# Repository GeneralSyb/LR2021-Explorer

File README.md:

# LR2021-Explorer
A small development board for Semtech's LR2021 4th generation LoRa transceiver.

## References
This design is based on the publicly available reference design available at:
https://www.semtech.com/products/wireless-rf/lora-plus/lr2021
The design uses a direct-tie implementation, which means there is no RF switch to switch between RX and TX mode. The reduces the component count, possibly at the loss of some performance.

## Testing
There is no Arduino-style library available yet, but some people are working on adding support for the chip in the RadioLib library. Therefore it is not know if this board actually works or not.

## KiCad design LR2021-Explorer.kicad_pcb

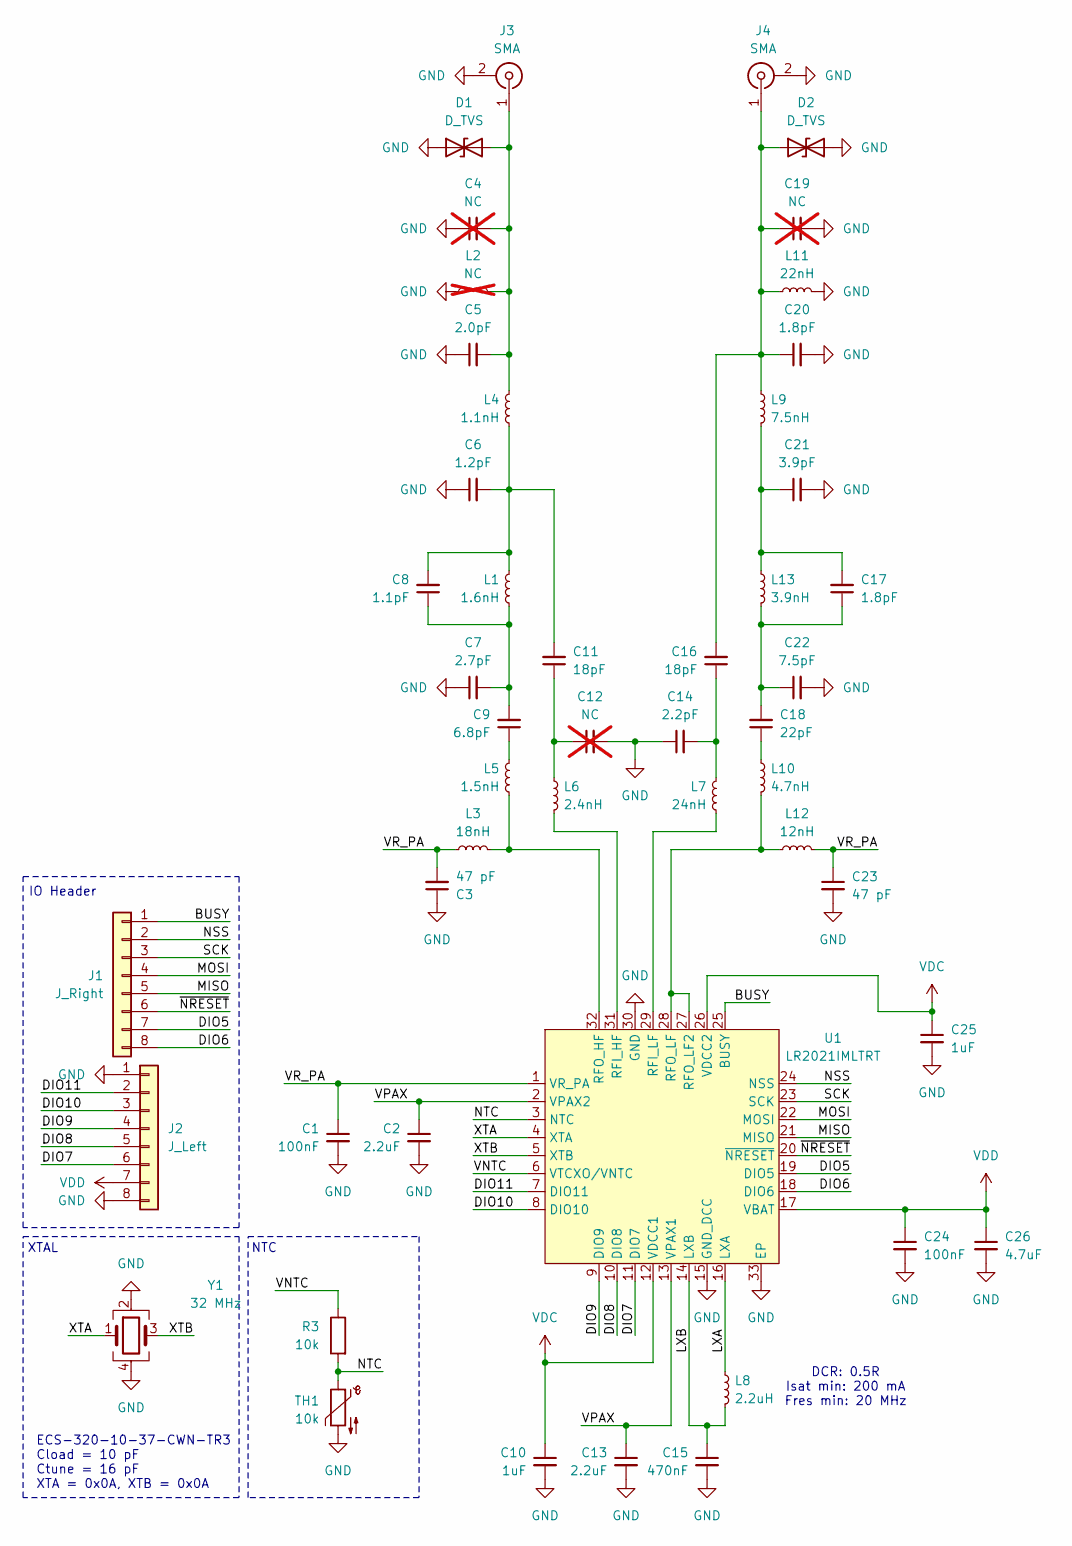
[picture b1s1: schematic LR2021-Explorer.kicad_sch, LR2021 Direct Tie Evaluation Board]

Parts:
C1, C24: 100nF; C_0402_1005Metric
C2, C13: 2.2uF; C_0402_1005Metric
C3, C23: 47 pF; C_0402_1005Metric
C4, C12, C19: NC; C_0402_1005Metric; not fitted
C5: 2.0pF; C_0402_1005Metric
C6: 1.2pF; C_0402_1005Metric
C7: 2.7pF; C_0402_1005Metric
C8: 1.1pF; C_0402_1005Metric
C9: 6.8pF; C_0402_1005Metric
C10, C25: 1uF; C_0402_1005Metric
C11, C16: 18pF; C_0402_1005Metric
C14: 2.2pF; C_0402_1005Metric
C15: 470nF; C_0402_1005Metric
C17, C20: 1.8pF; C_0402_1005Metric
C18: 22pF; C_0402_1005Metric
C21: 3.9pF; C_0402_1005Metric
C22: 7.5pF; C_0402_1005Metric
C26: 4.7uF; C_0805_2012Metric
D1, D2: D_TVS; D_0402_1005Metric
J1: J_Right; PinHeader_1x08_P2.54mm_Vertical
J2: J_Left; PinHeader_1x08_P2.54mm_Vertical
J3, J4: SMA; U.FL_Molex_MCRF_73412-0110_Vertical
L1: 1.6nH; L_0402_1005Metric
L2: NC; L_0402_1005Metric; not fitted
L3: 18nH; L_0402_1005Metric
L4: 1.1nH; L_0402_1005Metric
L5: 1.5nH; L_0402_1005Metric
L6: 2.4nH; L_0402_1005Metric
L7: 24nH; L_0402_1005Metric
L8: 2.2uH; L_0805_2012Metric
L9: 7.5nH; L_0402_1005Metric
L10: 4.7nH; L_0402_1005Metric
L11: 22nH; L_0402_1005Metric
L12: 12nH; L_0402_1005Metric
L13: 3.9nH; L_0402_1005Metric
R3: 10k; R_0402_1005Metric
TH1: 10k; R_0402_1005Metric
U1: LR2021IMLTRT; QFN-32-1EP_5x5mm_P0.5mm_EP3.7x3.7mm
Y1: 32 MHz; Crystal_SMD_2016-4Pin_2.0x1.6mm

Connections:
/BUSY: J1.1, U1.25 (BUSY)
/DIO5: J1.7, U1.19 (DIO5)
/DIO6: J1.8, U1.18 (DIO6)
/DIO7: J2.6, U1.11 (DIO7)
/DIO8: J2.5, U1.10 (DIO8)
/DIO9: J2.4, U1.9 (DIO9)
/DIO10: J2.3, U1.8 (DIO10)
/DIO11: J2.2, U1.7 (DIO11)
/LXA: L8.1, U1.16 (LXA)
/LXB: C15.1, L8.2, U1.14 (LXB)
/MISO: J1.5, U1.21 (MISO)
/MOSI: J1.4, U1.22 (MOSI)
/NSS: J1.2, U1.24 (NSS)
/NTC: R3.2, TH1.1, U1.3 (NTC)
/SCK: J1.3, U1.23 (SCK)
/VNTC: R3.1, U1.6 (VTCXO/VNTC)
/VPAX: C2.1, C13.1, U1.2 (VPAX2), U1.13 (VPAX1)
/VR_PA: C1.1, C3.2, C23.1, L3.1, L12.2, U1.1 (VR_PA)
/XTA: U1.4 (XTA), Y1.1
/XTB: U1.5 (XTB), Y1.3
/~NRESET: J1.6, U1.20 (~NRESET)
GND: C1.2, C2.2, C3.1, C4.1, C5.1, C6.1, C7.1, C10.2, C12.2, C13.2, C14.1, C15.2, C19.2, C20.2, C21.2, C22.2, C23.2, C24.2, C25.2, C26.2, D1.1 (A1), D2.2 (A2), J2.1, J2.8, J3.2 (Ext), J4.2 (Ext), L2.1, L11.2, TH1.2, U1.15 (GND_DCC), U1.30 (GND), U1.33 (EP), Y1.2, Y1.4
unnamed: C7.2, C8.1, C9.2, L1.2
unnamed: C9.1, L5.1
unnamed: C11.1, C12.1, L6.1
unnamed: C6.2, C8.2, C11.2, L1.1, L4.2
unnamed: C14.2, C16.1, L7.1
unnamed: C17.1, C18.2, C22.1, L13.2
unnamed: C17.2, C21.1, L9.2, L13.1
unnamed: C18.1, L10.1
unnamed: C4.2, C5.2, D1.2 (A2), J3.1 (In), L2.2, L4.1
unnamed: C16.2, C19.1, C20.1, D2.1 (A1), J4.1 (In), L9.1, L11.1
unnamed: L6.2, U1.31 (RFI_HF)
unnamed: L7.2, U1.29 (RFI_LF)
unnamed: L3.2, L5.2, U1.32 (RFO_HF)
unnamed: L10.2, L12.1, U1.27 (RFO_LF2), U1.28 (RFO_LF)
VDC: C10.1, C25.1, U1.12 (VDCC1), U1.26 (VDCC2)
VDD: C24.1, C26.1, J2.7, U1.17 (VBAT)

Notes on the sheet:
XTAL
NTC
ECS-320-10-37-CWN-TR3 Cload = 10 pF Ctune = 16 pF XTA = 0x0A, XTB = 0x0A
IO Header
DCR: 0.5R Isat min: 200 mA Fres min: 20 MHz

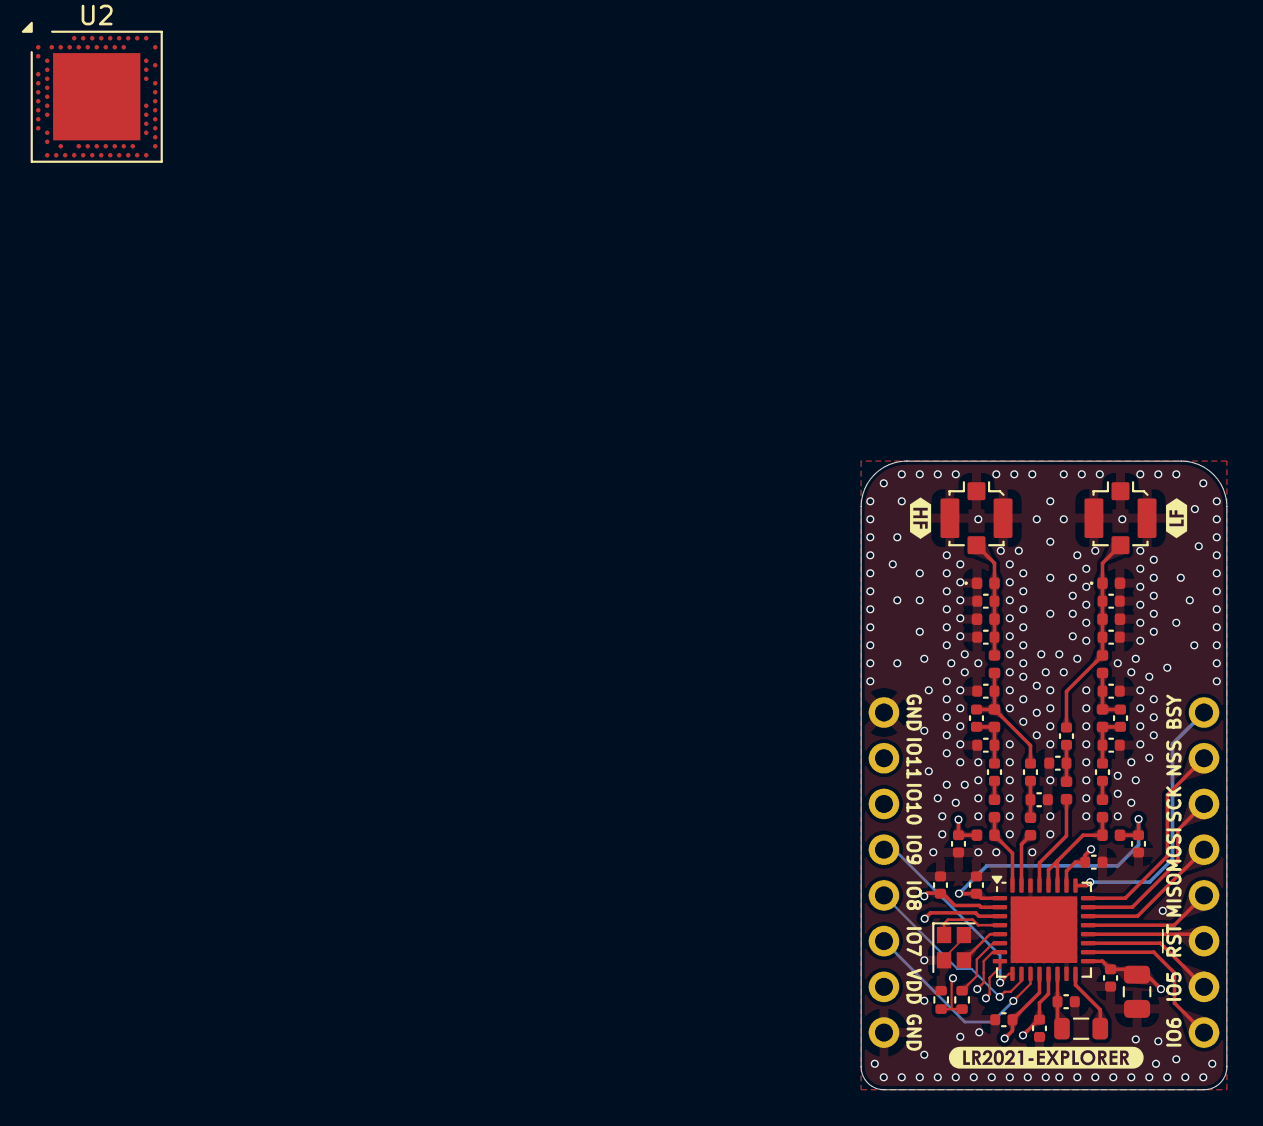
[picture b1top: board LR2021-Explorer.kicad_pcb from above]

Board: 4 copper layers, 20.3 x 34.9 mm, 53 parts (1 on the bottom side), 40 nets.

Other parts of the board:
U2: nRF52840; Nordic_AQFN-73-1EP_7x7mm_P0.5mm
kibuzzard-6920AF6E: G***; kibuzzard-6920AF6E
kibuzzard-6920AF52: G***; kibuzzard-6920AF52
kibuzzard-6920B030: G***; kibuzzard-6920B030

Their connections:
unnamed: U2.A22 (VDD), U2.AD14 (VDD), U2.AD23 (VDD), U2.B1 (VDD), U2.W1 (VDD)
unnamed: U2.B7 (VSS), U2.EP (VSS)

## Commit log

2025-12-12 Post-production upload
2025-12-13 Upload gerbers and docs
2026-01-25 Arduino program to measure the s parameters
    Possibly not working though...
2026-01-29 Add status and error read
